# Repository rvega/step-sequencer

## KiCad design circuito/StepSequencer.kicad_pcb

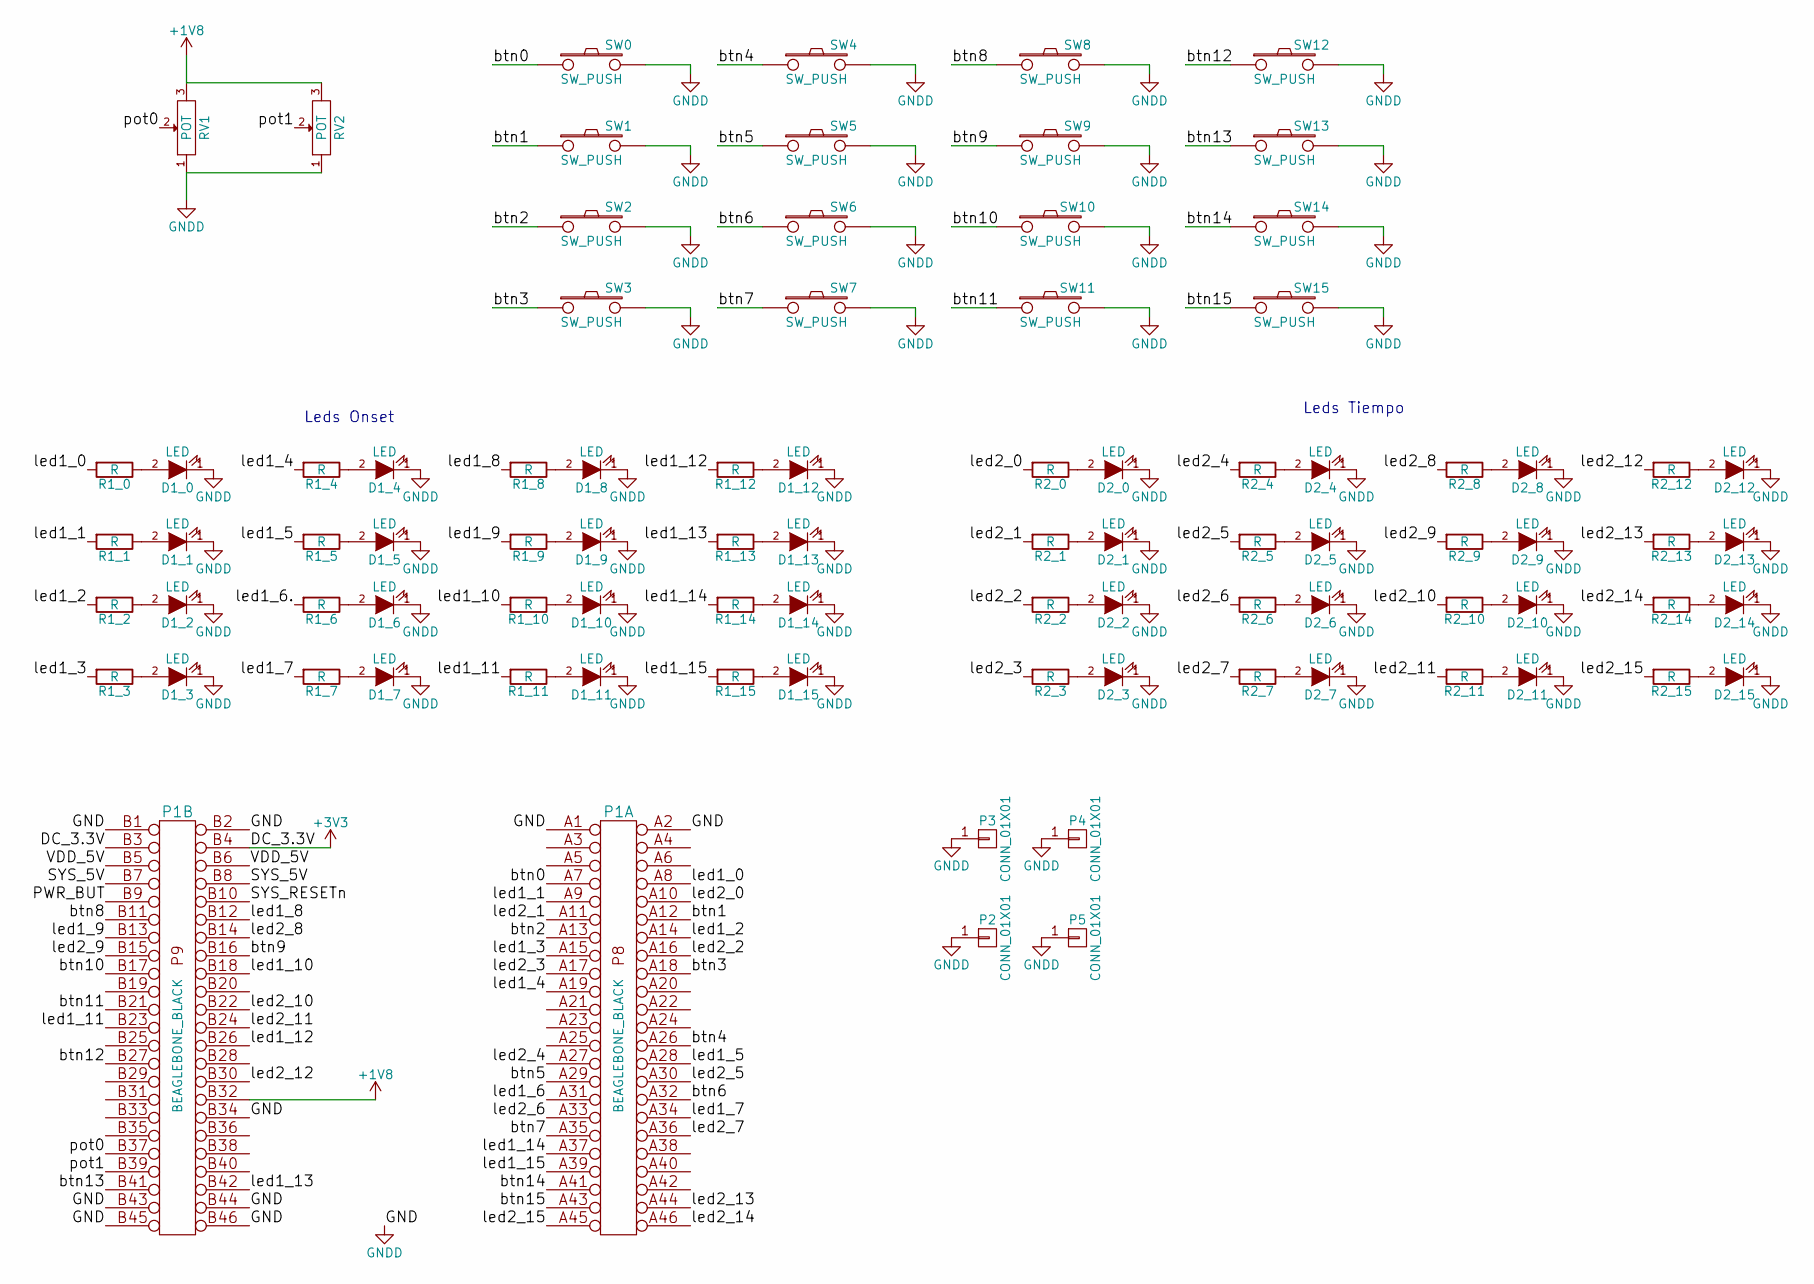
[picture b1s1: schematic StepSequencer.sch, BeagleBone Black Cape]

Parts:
D1_0, D1_1, D1_2, D1_3, D1_4, D1_5, D1_6, D1_7, D1_8, D1_9, D1_10, D1_11, D1_12, D1_13, D1_14, D1_15, D2_0, D2_1, D2_2, D2_3, D2_4, D2_5, D2_6, D2_7, D2_8, D2_9, D2_10, D2_11, D2_12, D2_13, D2_14, D2_15: LED; LED-3MM
P1: BEAGLEBONE_BLACK
P2, P3, P4, P5: CONN_01X01; SCREWS
R1_0, R1_1, R1_2, R1_3, R1_4, R1_5, R1_6, R1_7, R1_8, R1_9, R1_10, R1_11, R1_12, R1_13, R1_14, R1_15, R2_0, R2_1, R2_2, R2_3, R2_4, R2_5, R2_6, R2_7, R2_8, R2_9, R2_10, R2_11, R2_12, R2_13, R2_14, R2_15: R; Resistor_Horizontal_RM10mm
RV1, RV2: POT; POT_AZUL
SW0, SW1, SW2, SW3, SW4, SW5, SW6, SW7, SW8, SW9, SW10, SW11, SW12, SW13, SW14, SW15: SW_PUSH; BOTON

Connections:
+1V8: P1.B32 (P32), RV1.3, RV2.3
+3V3: P1.B3, P1.B4 (P4)
/SYS_5V: P1.B7 (P7), P1.B8 (P8)
/VDD_5V: P1.B5 (P5), P1.B6 (P6)
/btn0: P1.A7 (P7), SW0.1
/btn1: P1.A12 (P12), SW1.1
/btn2: P1.A13 (P13), SW2.1
/btn3: P1.A18 (P18), SW3.1
/btn4: P1.A26 (P26), SW4.1
/btn5: P1.A29 (P29), SW5.1
/btn6: P1.A32 (P32), SW6.1
/btn7: P1.A35 (P35), SW7.1
/btn8: P1.B11, SW8.1
/btn9: P1.B16 (P16), SW9.1
/btn10: P1.B17 (P17), SW10.1
/btn11: P1.B21 (P21), SW11.1
/btn12: P1.B27 (P27), SW12.1
/btn13: P1.B41 (P41), SW13.1
/btn14: P1.A41 (P41), SW14.1
/btn15: P1.A43 (P43), SW15.1
/led1_0: P1.A8 (P8), R1_0.2
/led1_1: P1.A9 (P9), R1_1.2
/led1_2: P1.A14 (P14), R1_2.2
/led1_3: P1.A15 (P15), R1_3.2
/led1_4: P1.A19 (P19), R1_4.2
/led1_5: P1.A28 (AP28), R1_5.2
/led1_7: P1.A34 (P34), R1_7.2
/led1_8: P1.B12 (P12), R1_8.2
/led1_9: P1.B13 (P13), R1_9.2
/led1_10: P1.B18 (P18), R1_10.2
/led1_11: P1.B23 (P23), R1_11.2
/led1_12: P1.B26 (P26), R1_12.2
/led1_13: P1.B42 (P42), R1_13.2
/led1_14: P1.A37 (P37), R1_14.2
/led1_15: P1.A39 (P39), R1_15.2
/led2_0: P1.A10 (P10), R2_0.2
/led2_1: P1.A11 (P11), R2_1.2
/led2_2: P1.A16 (P16), R2_2.2
/led2_3: P1.A17 (P17), R2_3.2
/led2_4: P1.A27 (P27), R2_4.2
/led2_5: P1.A30 (P30), R2_5.2
/led2_6: P1.A33 (P33), R2_6.2
/led2_7: P1.A36 (P36), R2_7.2
/led2_8: P1.B14 (P14), R2_8.2
/led2_9: P1.B15 (P15), R2_9.2
/led2_10: P1.B22 (P22), R2_10.2
/led2_11: P1.B24 (P24), R2_11.2
/led2_12: P1.B30 (P30), R2_12.2
/led2_13: P1.A44 (P44), R2_13.2
/led2_14: P1.A46 (P46), R2_14.2
/led2_15: P1.A45 (P45), R2_15.2
/pot0: P1.B37 (P37), RV1.2
/pot1: P1.B39 (P39), RV2.2
GNDD: D1_0.1 (K), D1_1.1 (K), D1_2.1 (K), D1_3.1 (K), D1_4.1 (K), D1_5.1 (K), D1_6.1 (K), D1_7.1 (K), D1_8.1 (K), D1_9.1 (K), D1_10.1 (K), D1_11.1 (K), D1_12.1 (K), D1_13.1 (K), D1_14.1 (K), D1_15.1 (K), D2_0.1 (K), D2_1.1 (K), D2_2.1 (K), D2_3.1 (K), D2_4.1 (K), D2_5.1 (K), D2_6.1 (K), D2_7.1 (K), D2_8.1 (K), D2_9.1 (K), D2_10.1 (K), D2_11.1 (K), D2_12.1 (K), D2_13.1 (K), D2_14.1 (K), D2_15.1 (K), P1.A1 (GND), P1.A2 (P2), P1.B1 (GND), P1.B2 (P2), P1.B34 (P34), P1.B43 (P43), P1.B44 (P44), P1.B45 (P45), P1.B46 (P46), P2.1, P3.1, P4.1, P5.1, RV1.1, RV2.1, SW0.2, SW1.2, SW2.2, SW3.2, SW4.2, SW5.2, SW6.2, SW7.2, SW8.2, SW9.2, SW10.2, SW11.2, SW12.2, SW13.2, SW14.2, SW15.2
unnamed: D1_0.2 (A), R1_0.1
unnamed: D1_1.2 (A), R1_1.1
unnamed: D1_2.2 (A), R1_2.1
unnamed: D1_3.2 (A), R1_3.1
unnamed: D1_4.2 (A), R1_4.1
unnamed: D1_5.2 (A), R1_5.1
unnamed: D1_6.2 (A), R1_6.1
unnamed: D1_7.2 (A), R1_7.1
unnamed: D1_8.2 (A), R1_8.1
unnamed: D1_9.2 (A), R1_9.1
unnamed: D1_10.2 (A), R1_10.1
unnamed: D1_11.2 (A), R1_11.1
unnamed: D1_12.2 (A), R1_12.1
unnamed: D1_13.2 (A), R1_13.1
unnamed: D1_14.2 (A), R1_14.1
unnamed: D1_15.2 (A), R1_15.1
unnamed: D2_0.2 (A), R2_0.1
unnamed: D2_1.2 (A), R2_1.1
unnamed: D2_2.2 (A), R2_2.1
unnamed: D2_3.2 (A), R2_3.1
unnamed: D2_4.2 (A), R2_4.1
unnamed: D2_5.2 (A), R2_5.1
unnamed: D2_6.2 (A), R2_6.1
unnamed: D2_7.2 (A), R2_7.1
unnamed: D2_8.2 (A), R2_8.1
unnamed: D2_9.2 (A), R2_9.1
unnamed: D2_10.2 (A), R2_10.1
unnamed: D2_11.2 (A), R2_11.1
unnamed: D2_12.2 (A), R2_12.1
unnamed: D2_13.2 (A), R2_13.1
unnamed: D2_14.2 (A), R2_14.1
unnamed: D2_15.2 (A), R2_15.1

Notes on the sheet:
Leds Onset
Leds Tiempo

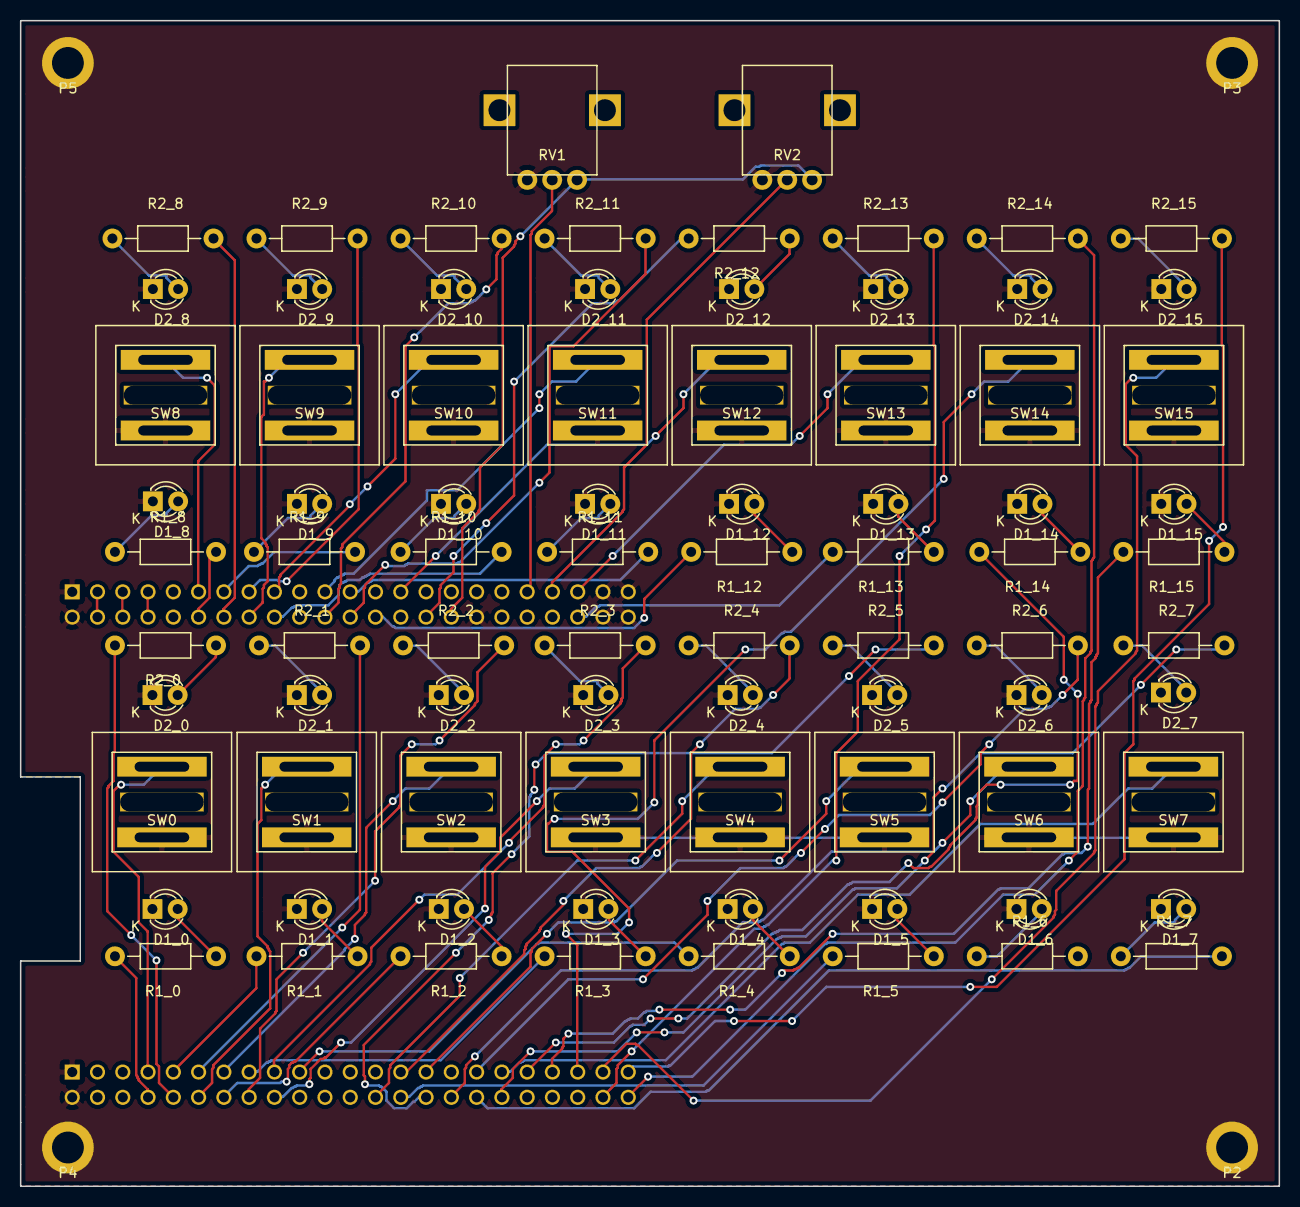
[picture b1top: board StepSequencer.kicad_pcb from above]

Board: 2 copper layers, 126.5 x 117.1 mm, 87 parts (1 on the bottom side), 86 nets.

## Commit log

2015-03-16 Init!
2015-03-16 Sarted sequencer external, some logic in place
2015-09-01 Importe nueva version de email del semestre pasado y modifique interfaz
2015-09-01 esquematico y maso la pcb
2015-09-01 Cad 3d caja (casi nada)
2015-09-08 Cambios en interfaz (api) del objeto sequencer, muestras de instrumentos colombianos.
2015-09-08 Version para Beagle del Patch.
2015-09-15 Empezando layout del pcb
2015-09-29 PBC ruteado de leds, botones, beagle, faltan pots y tierras.
2015-10-13 Botones viejos
2015-10-13 PCB Casi listo
2015-10-19 se genero u pad de tornillo 1/4, se dejo con la opcion pad para tornillos propuesta por la comunidad, no se han podido conectar a gnd
2015-10-20 Gato, gerber
2015-10-27 exportados gerber y drill, listos para la maquina
2015-11-03 arreglados huecos corte botones y botones footprints
2015-11-03 Arreglados huecos de botones, agregando modelos 3d de botones y pots
2015-12-01 cambios a proyecto de kikad
2015-12-01 avances en modelos cad de la caja
